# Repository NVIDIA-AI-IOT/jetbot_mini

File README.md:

# Jetbot Mini

This is the Jetbot Mini project, a smaller iteration of the [Jetbot](https://github.com/NVIDIA-AI-IOT/jetbot)! Some key features are as follows:
* Onboard motor controller and battery charger to reduce costs and wire clutter
* Custom baseboard for the Jetson Nano module
* A smaller chassis that can achieve two way traffic (i.e., two robots running on the road at the same time) on the LEGO roads used to test the original Jetbot
* Designed with KiCAD and Onshape for easy maker access

This project aims to be an accessible example project that uses the Jetson Nano platform and a custom baseboard, so any feedback about the design is welcome. 

**Please note that the A00 Baseboard design is not recommended for manufacture, as it requires a rework to work properly and some features have not been fully validated. The A01 Baseboard is currently in development that aims to fix issues found with A00.**

https://user-images.githubusercontent.com/46247601/129587346-760dd624-837d-4d27-9475-d30973f9e246.mp4

## Get Started and Involved!

Refer to [this](https://github.com/NVIDIA-AI-IOT/jetbot_mini/blob/main/docs/getting_started_with_A00.md) document to get a sense of how to use this repository and learn from this project!
This project is intended as a learning tool for makers, and any feedback related to the project is greatly appreciated!
* Report a bug by [creating an issue](https://github.com/NVIDIA-AI-IOT/jetbot_mini/issues)

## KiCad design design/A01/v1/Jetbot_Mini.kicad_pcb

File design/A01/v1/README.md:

# Setup

While developing the schematic and layout designs, I used some footprints from SnapEDA; in order to avoid dealing with licensing issues, I will not redistribute those files on this Github and instead link to where you can download the necessary files. 

## Symbol Library Setup

To get setup for the schematic, download the files and import the libraries "Jetbot Mini-rescue" and "Jetbot_Mini_Symbols" in the "libs" folder. 

In order to import a library, go through the following steps:
1. Download the .dcm and .lib files and remember where you stored them on your computer
2. Download the rest of the KiCAD files and open up the .pro file
3. Go to Preferences --> Manage Symbol Libraries --> Project Specific Libraries --> Add Existing Library to Table (folder icon on lower left of dialogue box)
4. Navigate to where the .lib files are stored on your computer and select the files
5. The libraries should be imported and when you try to add a component to the schematic, you should see the libraries show up

You may need the download the following symbol libraries from the KiCAD github: https://github.com/KiCad/kicad-symbols

| Library Name |
| :--- |
| Connector |
| Connector_Generic |
| Logic_LevelTranslator |

## Footprint Library Setup

To get setup for the layout design, you need the following SnapEDA footprint files (you need to make an account if you don't have one already, download the footprint and unzip the package):

| MPN | Device | Reference(s) | Link |
| :--- | :--- | :--- | :--- |
| 692121130100 | USB3 Type A | J8 | https://www.snapeda.com/parts/692121130100/Wurth%20Elektronik/view-part/4900658/?ref=search&t=692121130100 |
| 2309411-5 | DDR4 SODIMM Connector | J1 | https://www.snapeda.com/parts/2309411-5/TE%20Connectivity/view-part/2404627/?ref=search&t=2309411-5 |
| TPD1E05U06DPYR | ESD Diodes | D1, D9 | https://www.snapeda.com/parts/TPD1E05U06DPYR/Texas%20Instruments/view-part/383548/?ref=search&t=DIO_TPD1E05U06DPYR |
| BG300-04-A-L-A | Motor Header | J4 | https://www.snapeda.com/parts/BG300-04-A-L-A/Global%20Connector%20Technology/view-part/696206/?ref=search&t=BG300-04-A-L-A |
| LQH44PN100MP0L | 3V3 Buck Converter Inductor | L1 | https://www.snapeda.com/parts/LQH44PN100MP0L/Murata/view-part/?ref=dk&t=IND_LQH44PN100MP0L&con_ref=None |
| 1935161 | Battery Screw Terminal | J12 | https://www.snapeda.com/parts/1935161/Phoenix%20Contact/view-part/423515/?ref=search&t=1935161 |
| AP6503 | 3V3 Buck Converter | U17 | https://www.snapeda.com/parts/AP6503SP-13/Diodes%20Inc./view-part/562785/?ref=search&t=AP6503 |
| TPD4E05U06DQAR | ESD Diodes | U1, U2, U5, U7, U9, U20, U25, U28 | https://www.snapeda.com/parts/TPD4E05U06DQAR/Texas%20Instruments/view-part/431231/?ref=search&t=TPD4E05U06DQAR |
| 1N4148WT | Diode | D10 | https://www.snapeda.com/parts/1N4148WT/ON%20Semiconductor/view-part/2771069/?ref=search&t=1N4148WT |
| AT24C02D-MAHM-T | EEPROM | U22 | https://www.snapeda.com/parts/AT24C02D-MAHM-T/Microchip/view-part/229652/?ref=search&t=AT24C02D-MAHM-T |
| 74LVC4245A | Level Shifter | U23 | https://www.snapeda.com/parts/74LVC4245APW/Nexperia%20USA/view-part/557968/?ref=search&t=74LVC4245A%20 |
| 74LVC1G126W5-7, 74LVC1G07W5-7 | Tri-State Buffer | U11, U12, U14, U31 | https://www.snapeda.com/parts/74LVC1G126W5-7/Diodes%20Inc./view-part/234182/?ref=search&t=74LVC1G126W5-7 |
| B3SL-1022P | Push Button | SW1 | https://www.snapeda.com/parts/B3SL-1022P/Omron/view-part/215208/?ref=search&t=B3SL-1022P |
| 1-1734248-5 | Camera Connectors | J2, J3 | https://www.snapeda.com/parts/1-1734248-5/TE%20Connectivity/view-part/?ref=te_in&t=1-1734248-5&con_ref=None |
| B340A-13-F | Schottky Diode | D5, D8 | https://www.snapeda.com/parts/B340A-13-F/Diodes%20Inc./view-part/78704/?ref=search&t=B340A-13_F |
| LQH44PN100MP0L | 10uH Inductor for 3V3 Buck | L1 | https://www.snapeda.com/parts/LQH44PN100MP0L/Murata/view-part/4547005/?ref=search&t=LQH44PN100MP |

In order to import the footprints, go through the following steps:
1. Download the KiCAD files to your computer
2. Open the .pro file and click "Footprint Editor" on the top ribbon, the icon is a 6 pin package with green pins
3. Go to File --> New Library --> Create library with name of your choice (should have .pretty extension) in place of your choice, it is typical to keep everything with the KiCAD files --> Choose local
4. Your library should be created, then add the .kicad_mod files from the downloaded SnapEDA folders to the .pretty folder
5. Open up the schematic and go to "Assign PCB footprints to schematic symbols" on the top ribbon, and assign the footprints from your custom library to each of the corresponding symbols

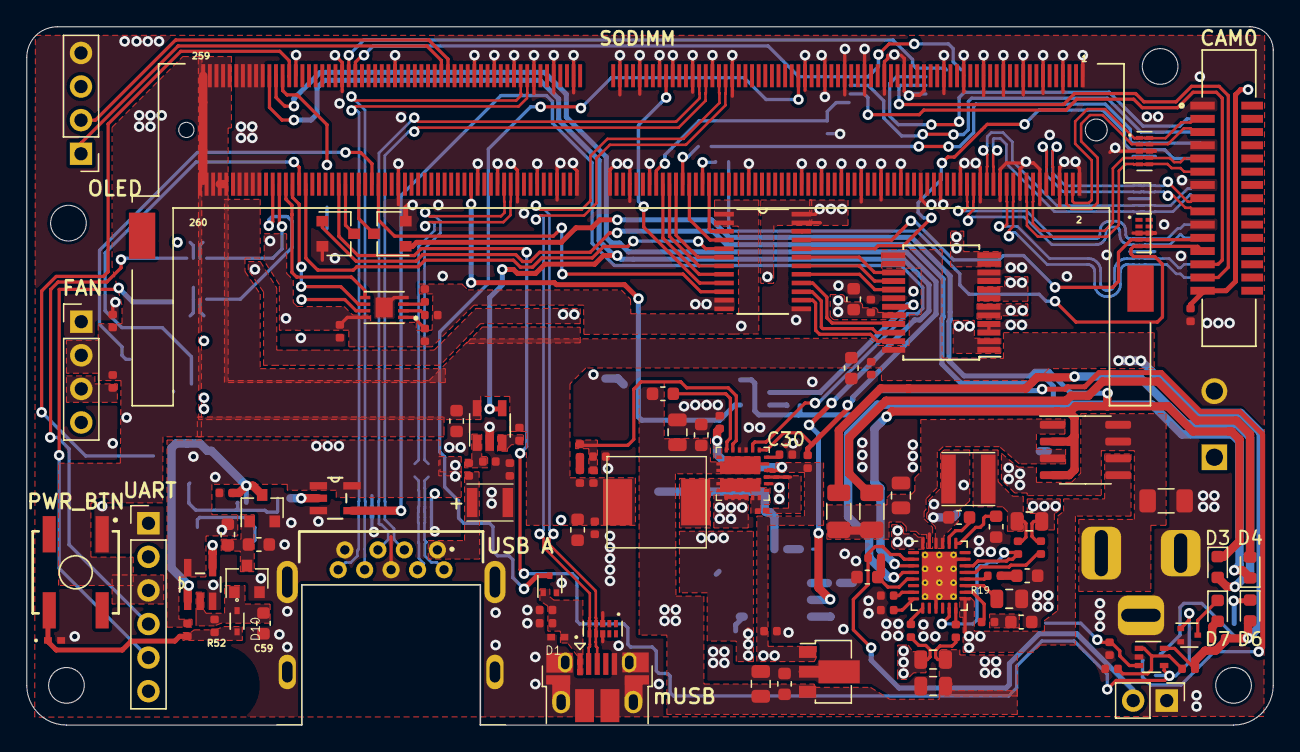
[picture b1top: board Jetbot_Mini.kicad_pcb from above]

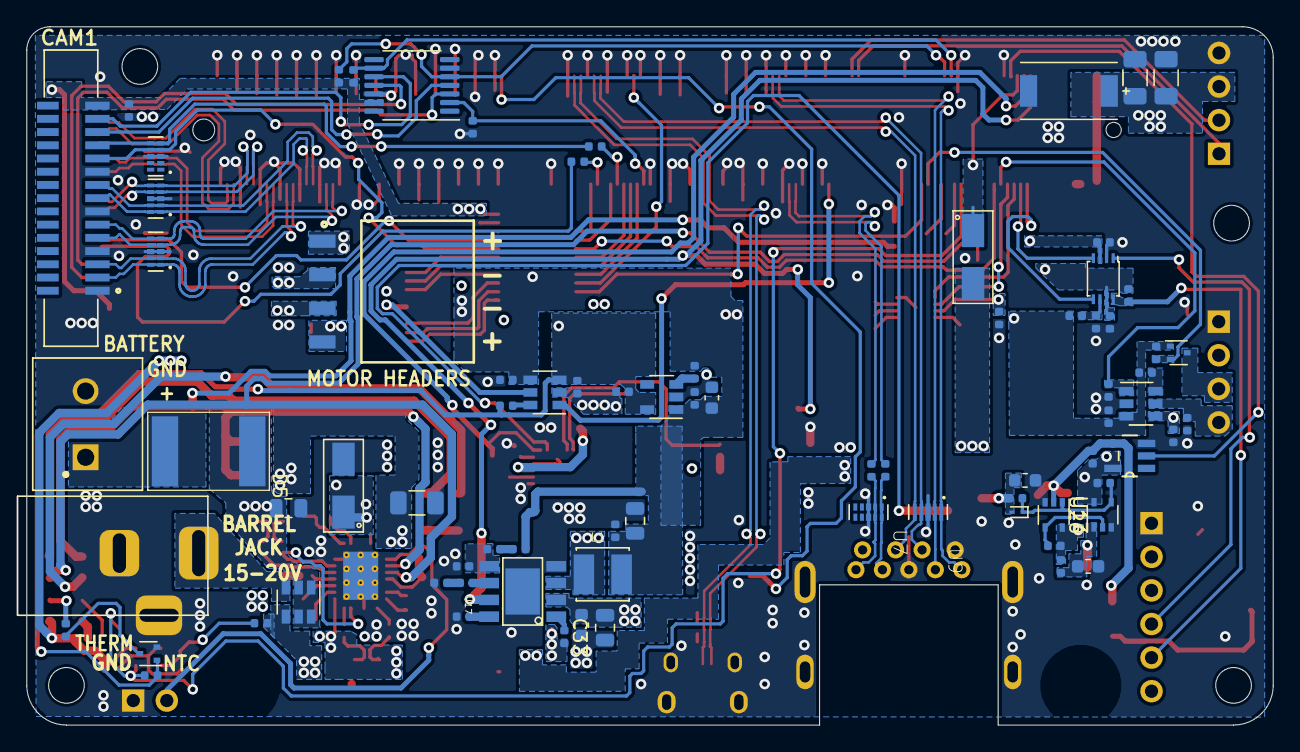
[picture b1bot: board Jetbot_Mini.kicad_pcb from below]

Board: 4 copper layers, 94.2 x 52.8 mm, 188 parts (79 on the bottom side), 155 nets.

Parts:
C1, C2, C3, C5, C7, C8, C10, C12, C13, C25, C28, C29, C42, C45, C49, C51, C52, C53, C54, C55, C56, C57, C58: 0.1uF; C_0402_1005Metric
C4, C6, C9, C14, C59: 10uF; C_0603_1608Metric
C11: 120uF; 6TPG150MZG
C15: 4.7uF; C_0603_1608Metric
C16: 0.47uF; C_0402_1005Metric
C17, C21, C50: 1uF; C_0603_1608Metric
C18, C27, C34, C35, C44: 0.1uF; C_0603_1608Metric
C19: 0.33uF; C_0805_2012Metric
C20, C23: 10uF; C_1206_3216Metric
C22, C37, C38, C40: 22uF; C_0805_2012Metric
C24: 4.7uF; C_0805_2012Metric
C26, C31: 2.2nF; C_0603_1608Metric
C30, C33: 10nF; C_0402_1005Metric
C32: 6.8nF; C_0402_1005Metric
C36: 2.2nF; C_0201_0603Metric
C39: 47uF; C_0805_2012Metric
C41: Coption; C_0402_1005Metric
C43: 22uF; C_0603_1608Metric
C46: 330uF; 6TPE330MAP
C47, C48: 100uF; C_1206_3216Metric
D1, D9: TPD1E10B06DPYR; DIO_TPD1E05U06DPYR
D2: NSR0620P2T5G; D_SOD-923
D3, D4, D6, D7: LED; LED_0603_1608Metric
D5, D8: B340A-13-F; B340A-13_F
D10: 1N4148WT; SODFL1608X70N
F1: 2920L185DR; 2920_(7351_metric)
H1, H2, H3, H4: MountingHole; MountingHole_2.7mm_M2.5_ISO7380
J1: nvidia_nano_NANO; TE_2309411-5
J2, J3: Conn_01x15_fixed_pin; TE_1-1734248-5
J4: BG300-04-A-L-A; GCT_BG300-04-X-X-A_REVC
J5: Barrel_Jack_Switch; DC_JACK_DC-005-5A-2.5_mirrored
J6: Conn_01x02; PinHeader_1x02_P2.54mm_Vertical
J7: USB_B_Micro_correct_pin; USB_Micro-B_Amphenol_10103594-0001LF_Horizontal
J8: USB3_A; 692121130100_no_edge
J9: Conn_01x04; PinHeader_1x04_P2.54mm_Vertical
J12: 1935161; PHOENIX_1935161
J13: OLED; PinHeader_1x04_P2.54mm_Vertical
J14: Conn_01x06; PinHeader_1x06_P2.54mm_Vertical
L1: 10uH; IND_LQH44PN100MP0L
L2: 10uH; inductor_10uH_2.4A
L3: 4.7uH; MWSA0603-4R7MT
Q1, Q2: DMN26D0UT-7; SOT-523
Q3, Q4: 2N7002; SOT-23
Q5, Q8: DMG1012T; SOT-523
Q6, Q7: 2N7002,215; SC-59
R1, R2, R34, R40, R49, R60, R61: 0; R_0402_1005Metric
R3, R4: 1.6k; R_0402_1005Metric
R5, R6, R9, R10, R11, R12, R15, R16, R17, R18, R22, R26, R31, R39, R42, R46, R48, R51, R53, R55, R56, R57, R59: 10k; R_0402_1005Metric
R7: 1M; R_0402_1005Metric
R8, R21, R50, R54: 100k; R_0402_1005Metric
R13: 2.7M; R_0603_1608Metric
R14, R43: 4.7k; R_0402_1005Metric
R19: 0; R_0805_2012Metric
R20: 470k; R_0402_1005Metric
R23, R24: 1k; R_1206_3216Metric
R25: 2.7k; R_0402_1005Metric
R27, R29: 50; R_0402_1005Metric
R28: 20m; R_0805_2012Metric
R30: 750; R_0402_1005Metric
R32: 6.8k; R_0402_1005Metric
R33: 1.3M; R_0603_1608Metric
R35: 26.1k; R_0402_1005Metric
R36, R37: 402; R_0402_1005Metric
R38: 160m; R_0805_2012Metric
R41: 56k; R_0402_1005Metric
R44: 5.1k; R_0402_1005Metric
R45: 18.7k; R_0402_1005Metric
R47, R58: 150; R_0402_1005Metric
R52: 22k; R_0402_1005Metric
SW1: B3SL-1022P; SW_B3SL-1022P
U1, U2, U5, U7, U9, U25, U28, U30: TPD4E05U06DQAR; TI_TPD4E05U06DQAR
U3: DMP3056LDM-7; SOT-23-6
U4: analog_TC7USB40FT_2; TSSOP-14_4.4x5mm_P0.65mm
U6: TB6612FNG; SSOP-24_5.3x8.2mm_P0.65mm
U8: RT9742CGJ5; TSOT-23-5
U10, U20: PI4ULS5V201TAEX; SOT-23-6
U11, U14: 74LVC1G126W5-7; SOT95P280X145-5N
U12: 74LVC1G07W5-7; SOT95P280X145-5N
U13, U26: MC74VHC1G01DFT1G; SOT-353_SC-70-5
U15: AS78L05; SOT-89-3
U16: MP2619; QFN-28-1EP_4x5mm_P0.5mm_EP2.65x3.65mm_ThermalVias
U17: AP6503; SO-8EP
U18: GS9238
U19: LMV331SE-7; SOT-353_SC-70-5
U21: TXB0102DCU; VSSOP-8_2.4x2.1mm_P0.5mm
U22: AT24C02D-MAHM-T; SON50P200X300X60-9N
U23: 74LVC4245A; SOP65P640X110-24N
U24: TLV70218DBVR_SOT23-5; SOT-23-5
U27: DMP3056LSD-13; SOIC-8_3.9x4.9mm_P1.27mm

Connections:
+1V8: C51.1, C52.1, C53.1, C54.1, C57.1, Q2.1, Q8.1, R9.1, R10.1, R48.1, R49.1, R55.1, R56.1, R57.1, R59.1, U10.3, U20.3, U21.3, U22.8, U23.1, U23.2, U24.5
+3V3: C1.1, C2.1, C3.1, C4.1, C39.1, C42.1, C49.1, C50.1, C55.1, C56.1, J2.15, J3.15, L1.2, R3.1, R4.1, R34.1, R51.1, R54.1, U4.13, U6.20, U10.4, U21.7, U23.23, U23.24, U24.1
+5V: C5.1, C6.1, C9.1, C13.1, C41.1, C43.1, C45.1, C46.1, C47.1, C48.1, C58.1, D6.2, J1.251, J1.252, J1.253, J1.254, J1.255, J1.256, J1.257, J1.258, J1.259, J1.260, J9.2, J13.3, J14.3, L3.2, R6.1, R12.1, R40.1, R43.1, R58.1, U6.13, U6.14, U6.24, U8.5, U19.5, U20.4
+5V_AO: C25.1, C28.1, D8.2, R13.1, R14.1, R15.1, R16.1, R17.1, R18.1, R31.1, U11.5, U12.5, U13.5, U14.1, U14.5, U15.1, U18.7, U18.21, U26.5
+12V: C18.1, C19.1, C22.1, C27.1, C37.1, C38.1, C44.1, R28.1, R29.1, R33.1, R45.1, U3.4, U15.3, U17.2, U18.8, U18.9, U18.22, U18.24
/Camera/CAM0_I2C_SCL: J2.13, U4.3
/Camera/CAM0_I2C_SDA: J2.14, U4.11
/Camera/CAM0_MCLK: J2.12, R1.2, U1.5, U1.6
/Camera/CAM0_MCLK_NANO: J1.116, R1.1
/Camera/CAM0_PWDN_1V8: J1.114, U23.3
/Camera/CAM0_PWDN_3V3: J2.11, U1.4, U1.7, U23.21
/Camera/CAM1_I2C_SCL: J3.13, U4.4
/Camera/CAM1_I2C_SDA: J3.14, U4.10
/Camera/CAM1_MCLK: J3.12, R2.2, U28.5, U28.6
/Camera/CAM1_MCLK_NANO: J1.122, R2.1
/Camera/CAM1_PWDN_1V8: J1.120, U23.4
/Camera/CAM1_PWDN_3V3: J3.11, U23.20, U28.4, U28.7
/Camera/CAM_I2C_SCL: J1.213, R3.2, U4.5
/Camera/CAM_I2C_SDA: J1.215, R4.2, U4.9
/Camera/CAM_SEL: J1.130, R5.1, U4.2
/Camera/CSI0_CLK_N: J1.10, J2.8, U30.5, U30.6
/Camera/CSI0_CLK_P: J1.12, J2.9, U30.4, U30.7
/Camera/CSI0_D0_N: J1.4, J2.2, U5.1, U5.10
/Camera/CSI0_D0_P: J1.6, J2.3, U5.2, U5.9
/Camera/CSI0_D1_N: J1.16, J2.5, U5.4, U5.7
/Camera/CSI0_D1_P: J1.18, J2.6, U5.5, U5.6
/Camera/CSI2_CLK_N: J1.28, J3.8, U30.1, U30.10
/Camera/CSI2_CLK_P: J1.30, J3.9, U30.2, U30.9
/Camera/CSI2_D0_N: J1.22, J3.2, U2.1, U2.10
/Camera/CSI2_D0_P: J1.24, J3.3, U2.2, U2.9
/Camera/CSI2_D1_N: J1.34, J3.5, U2.4, U2.7
/Camera/CSI2_D1_P: J1.36, J3.6, U2.5, U2.6
/Fan/FAN_HEADER_PWM: J9.4, R11.1, U20.5
/Fan/FAN_HEADER_TACH: J9.3, Q2.3, R12.2
/Fan/FAN_LVL_OE: R9.2, U20.6
/Fan/FAN_PWM: J1.230, R8.1, U20.1
/Fan/FAN_TACH: J1.208, Q2.2, R10.2
/Motors/LVL_SHIFT_OE: R59.2, U10.6
/Motors/M1+: J4.4, U6.1, U6.2
/Motors/M1-: J4.3, U6.5, U6.6
/Motors/M2+: J4.1, U6.11, U6.12
/Motors/M2-: J4.2, U6.7, U6.8
/Motors/MC_A1: U6.21, U23.16
/Motors/MC_A2: U6.22, U23.15
/Motors/MC_B1: U6.17, U23.17
/Motors/MC_B2: U6.16, U23.18
/Motors/MC_PWM_A: U6.23, U23.14
/Motors/MC_PWM_B: U6.15, U23.19
/Motors/MOTOR_CNTRL_STBY: U6.19, U10.5
/Motors/~MOD_SLEEP: J1.178, U10.1
/Nano_IO/CHARGER_~ACOK: D3.1, Q6.1, U16.3, U27.2, U27.4
/Nano_IO/CHARGER_~CHGOK: D4.1, Q7.1, U16.4
/Nano_IO/EEPROM_A0: R55.2, U22.1
/Nano_IO/EEPROM_A1: R56.2, U22.2
/Nano_IO/EEPROM_A2: R57.2, U22.3
/Nano_IO/EEPROM_WP: R53.1, U22.7
/Nano_IO/I2C0_SCL: J1.185, J13.2
/Nano_IO/I2C0_SDA: J1.187, J13.1
/Nano_IO/I2C2_SCL: J1.232, U22.6
/Nano_IO/I2C2_SDA: J1.234, U22.5
/Nano_IO/LOW_VOLTAGE_WARNING: J1.218, Q5.1, R48.2, U19.4
/Nano_IO/LVL_SHIFT_EN: R49.2, R50.1, U21.6
/Nano_IO/MC_A1_1V8: J1.128, U23.8
/Nano_IO/MC_A2_1V8: J1.127, U23.9
/Nano_IO/MC_B1_1V8: J1.126, U23.7
/Nano_IO/MC_B2_1V8: J1.124, U23.6
/Nano_IO/MC_PWM_A_1V8: J1.206, U23.10
/Nano_IO/MC_PWM_B_1V8: J1.228, U23.5
/Nano_IO/NANO_CHARGER_~ACOK: J1.212, Q6.3
/Nano_IO/NANO_CHARGER_~CHGOK: J1.216, Q7.3
/Nano_IO/PMIC_BBAT: D8.1, J1.235
/Nano_IO/SHUTDOWN_REQ: J1.233, U12.2
/Nano_IO/UART_DEBUG_RX_1V8: J1.238, U21.5
/Nano_IO/UART_DEBUG_RX_3V3: J14.5, R54.2, U21.8
/Nano_IO/UART_DEBUG_TX_1V8: J1.236, U21.4
/Nano_IO/UART_DEBUG_TX_3V3: J14.4, U21.1
/Nano_IO/VBUS_DET: J1.87, Q1.3
/Power_1/BARREL_JACK_VIN: C20.1, C23.1, J5.1, U3.3, U16.28, U27.7, U27.8
/Power_1/BATTERY_OUTPUT: C40.1, F1.2, R37.1, R38.1, U3.1, U3.2, U3.5, U3.6
/Power_1/Battery_PWR: F1.1, J12.1
/Power_1/CHARGER_BATT: R37.2, U16.19
/Power_1/CHARGER_BST: C35.2, U16.24
/Power_1/CHARGER_CELLS: R19.1, U16.17
/Power_1/CHARGER_COMPI: R30.1, U16.18
/Power_1/CHARGER_COMPV: R25.1, U16.16
/Power_1/CHARGER_CSP: R36.2, U16.13, U16.20
/Power_1/CHARGER_EN: R26.1, U16.7
/Power_1/CHARGER_NTC: J6.2, R21.2, U16.2
/Power_1/CHARGER_PIN: C24.1, R23.2, R24.2, U16.27, U27.1, U27.3
/Power_1/CHARGER_RG1: R27.2, U16.9
/Power_1/CHARGER_RG2: R29.2, U16.14
/Power_1/CHARGER_SHDN: R22.1, U16.8
/Power_1/CHARGER_SW1: C35.1, D5.1, L2.1, U16.25, U16.26
/Power_1/CHARGER_TMR: C34.1, U16.23
/Power_1/CHARGER_VCC: R27.1, R28.2, U16.15, U27.5, U27.6
/Power_1/CHARGER_VREF33: C21.1, R21.1, U16.5
/Power_1/COMPI_CAP: C31.2, R30.2
/Power_1/COMPV_CAP: C26.2, R25.2
/Power_1/IND_SW_OUT: L2.2, R36.1, R38.2
/Power_1/RES_ACOK: D3.2, R23.1
/Power_1/RES_CHGOK: D4.2, R24.1
/Power_2/1V8_REG_EN: R51.2, U24.3
/Power_2/COMPARATOR_V+: R43.2, R44.1, U19.1
/Power_2/COMPARATOR_V-: R45.2, R46.2, U19.3
/Power_2/FET_SOURCE_LV: D7.1, Q5.3
/Power_2/FET_SOURCE_PWR: Q8.3, R47.2
/Power_2/LED_CATHODE_LV: D7.2, R58.2
/Power_2/LED_CATHODE_PWR: D6.1, R47.1
/Power_3/3.3V_BUCK_PWR_EN: J1.239, U8.4, U17.7
/Power_3/3V3_BUCK_BST: C33.1, U17.1
/Power_3/3V3_BUCK_COMP: C32.1, U17.6
/Power_3/3V3_BUCK_FB: R35.2, R39.1, U17.5
/Power_3/3V3_BUCK_SS: C29.1, U17.8
/Power_3/3V3_BUCK_SW: C33.2, L1.1, U17.3
/Power_3/5V_BUCK_BOOT: C36.1, U18.20
/Power_3/5V_BUCK_FB: C41.2, R41.2, R42.1, U18.5
/Power_3/5V_BUCK_LX: C36.2, L3.1, U18.10, U18.11, U18.16, U18.17, U18.18, U18.25
/Power_3/5V_BUCK_PWR_EN: U14.4, U18.2
/Power_3/5V_BUCK_SS: C30.1, U18.23
/Power_3/5V_BUCK_TON: R33.2, U18.6
/Power_3/PGOOD: J1.237, R31.2, U18.1
/Power_Logic/10s_THRESHOLD: C14.1, Q3.3, Q4.1, R13.2
/Power_Logic/BTN_OUT: D9.1, D10.2, R15.2, R52.1, SW1.2
/Power_Logic/BUTTON_OUTPUT: C59.1, D10.1, Q3.1, R52.2, U11.2
/Power_Logic/PWR_CNTRL_BEFORE_BUFFER: C17.1, D2.2, R20.1, U14.2
/Power_Logic/RESET_FB: D2.1, R18.2, R20.2, U13.1, U26.4
/Power_Logic/SET: C15.1, R14.2, U11.4, U26.1
/Power_Logic/SET_FB: R17.2, U13.4, U26.2
/USB/Nano_SS_TX_C+: C8.1, J1.168
/USB/Nano_SS_TX_C-: C7.1, J1.166
/USB/SS_RX+: J1.163, J8.6, U9.2, U9.9
/USB/SS_RX-: J1.161, J8.5, U9.1, U9.10
/USB/SS_TX_C+: C8.2, J8.9, U7.2, U7.9
/USB/SS_TX_C-: C7.2, J8.8, U7.1, U7.10
/USB/USB0+: J1.111, J7.3, U25.4, U25.7
/USB/USB0-: J1.109, J7.2, U25.5, U25.6
/USB/USB1+: J1.117, J8.3, U9.4, U9.7
/USB/USB1-: J1.115, J8.2, U9.5, U9.6
/USB/USB_SWITCH_FLG: R6.2, U8.3
/USB/USB_SWITCH_OUTPUT: C12.1, R60.2, U8.1
/USB/uVBUS: C10.1, D1.1, J7.1, Q1.1, R7.1
GND: C1.2, C2.2, C3.2, C4.2, C5.2, C6.2, C9.2, C10.2, C11.2, C12.2, C13.2, C14.2, C15.2, C16.2, C17.2, C18.2, C19.2, C20.2, C21.2, C22.2, C23.2, C24.2, C25.2, C26.1, C27.2, C28.2, C29.2, C30.2, C31.1, C34.2, C37.2, C38.2, C39.2, C40.2, C42.2, C43.2, C44.2, C45.2, C46.2, C47.2, C48.2, C49.2, C50.2, C51.2, C52.2, C53.2, C54.2, C55.2, C56.2, C57.2, C58.2, C59.2, D1.2, D5.2, D9.2, J1.1, J1.2, J1.7, J1.8, J1.13, J1.14, J1.19, J1.20, J1.25, J1.26, J1.31, J1.32, J1.37, J1.38, J1.43, J1.44, J1.49, J1.50, J1.55, J1.56, J1.61, J1.62, J1.67, J1.68, J1.73, J1.74, J1.79, J1.80, J1.85, J1.86, J1.102, J1.107, J1.113, J1.119, J1.125, J1.129, J1.132, J1.135, J1.138, J1.141, J1.144, J1.146, J1.147, J1.152, J1.153, J1.158, J1.159, J1.164, J1.165, J1.170, J1.171, J1.176, J1.177, J1.200, J1.201, J1.217, J1.231, J1.241, J1.242, J1.243, J1.244, J1.245, J1.246, J1.247, J1.248, J1.249, J1.250, J2.1, J2.4, J2.7, J2.10, J3.1, J3.4, J3.7, J3.10, J5.2, J5.3, J6.1, J7.5, J7.6, J8.4, J8.7, J8.10, J9.1, J12.2, J13.4, J14.1, Q1.2, Q3.2, Q4.2, Q5.2, Q6.2, Q7.2, Q8.2, R5.2, R7.2, R8.2, R11.2, R19.2, R22.2, R26.2, R32.2, R39.2, R42.2, R44.2, R46.1, R50.2, R53.2, R61.1, R61.2, SW1.1, U1.3, U1.8, U2.3, U2.8, U4.6, U4.12, U5.3, U5.8, U6.3, U6.4, U6.9, U6.10, U6.18, U7.3, U7.8, U8.2, U9.3, U9.8, U10.2, U11.3, U12.3, U13.3, U14.3, U15.2, U16.11, U16.21, U16.29, U17.4, U17.9, U18.3, U18.4, U18.12, U18.13, U18.14, U18.15, U18.19, U19.2, U20.2, U21.2, U22.4, U22.9, U23.11, U23.12, U23.13, U23.22, U24.2, U25.3, U25.8, U26.3, U28.3, U28.8, U30.3, U30.8
LATCH_RESET: C16.1, Q4.3, R16.2, U11.1, U12.4, U13.2
unnamed: C32.2, R32.1
unnamed: R34.2, R35.1
unnamed: R40.2, R41.1
unnamed: U1.1, U1.10
unnamed: U1.2, U1.9
unnamed: U7.4, U7.7
unnamed: U7.5, U7.6
unnamed: U25.1, U25.10
unnamed: U25.2, U25.9
unnamed: U28.1, U28.10
unnamed: U28.2, U28.9
VBUS: C11.1, J8.1, R60.1

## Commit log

2021-07-23 Add files via upload
    Added A01 Rev3 schematic as test file.
2021-07-23 Create A01_placeholder
2021-07-30 Create Rev_1_Placeholder
2021-07-30 Create Rev_2_Placeholder
2021-08-03 Added A00 Design Files
    Did not include any 3D models or footprints
2021-08-11 Add files via upload
    Uploading some more renderings of Jetbot Mini with shorter battery wire
2021-08-11 Add files via upload
    Uploading more renderings of Jetbot Mini with shorter battery cable
2021-08-11 Delete Jetbot_Mini_v9_Inner.jpg
    going to add cropped version
2021-08-11 Add files via upload
    Added image to be used in README
2021-08-11 Update README.md
    Added demo video
2021-08-16 Rename Jetbot_Mini_Chassis_v9.md to Jetbot_Mini_Chassis_v9_Description.md
2021-08-17 Rename design_justification.md to A00_design_justification.md
2021-08-18 Rename A00_bringup.md to A00_bringup_rework.md
2021-08-18 Rename bringup_rework.md to A00_bringup_rework.md
